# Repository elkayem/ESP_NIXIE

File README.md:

# ESP_NIXIE

Building a Nixie Clock is a time honored tradition among makers, and this is yet another DIY Nixie Clock project.  This one is unique in a few respects: 1) it uses an ESP8266 development board as the microcontroller, allowing it to automatically sync its time to NIST over WiFi, and 2) it features a 3D printed frame and hand-solderable PCB. 

These electronics have also been incorporated into a ceramic case by the talented artist [Jackson Fyfe](https://www.jacksonfyfeceramics.com/).  The case you see pictured above is one he created for me.  Head over to his website to see a number of his other stunning Nixie case designs, which he is selling as a limited release.

This repository contains the code, and schematics for driving a Nixie tube clock with a NodeMCU 1.0 ESP8266 development board.  STL files are also provided for a 3D printed case.  Two variants of the PCB and 3D printed cases are available, a PCB and case without a colon separator circuit, and a PCB and case with a colon separator circuit.  The code is the same, with a single #define statement that can be commented to compile the option without the separator circuit.   

When the clock is turned on for the first time, it will create a WiFi access point at ESPNIXIE that can be connected to using a computer or smartphone.  The user can use this access point to specify the WiFi network SSID and password.  This information is stored in EEPROM, so will not be needed the next time the clock is turned on.  It uses the Arduino [Wifi Manager](https://github.com/tzapu/WiFiManager) to create the access point.  

This clock includes a menu-driven OLED screen and rotary encoder, with menu options described below.  All settings are stored in EEPROM so they can be used after a power cycle.
* *Set UTC Offset.*  The user's local time zone is selected by adjusting the time offset from UTC time.
* *Auto DST.* This option enables/disables automatic daylight savings time.  The code includes rules for US Daylight Savings Time (second Sunday in March at 2am to first Sunday in November at 2am).  The code can easily be modified for rules in other countries.
* *12/24 Hours.* This option selects between 12 and 24 hour time formats.
* *Blink Colon.* This option is available if using a colon separator.  If enabled, it will blink the colon once per second, otherwise it will keep the colon on steady.  This option is not available if #define CLOCK_COLON is commented in the code.  
* *Protect Cathode.* Nixie tubes are susceptible to cathode poisoning when material from an active cathode sputters on the inactive cathodes.  This process can be reversed by occasionally cycling through all numbers for short durations.  When enabled, this feature will cycle through all the numbers at a 10 Hz rate for 5 seconds.  Besides protecting the cathodes, it also looks cool.  Time intervals ranging from 15 minutes to two hours can be selected.
* *Auto Shutoff.* When enabled, this feature will automatically turn off the tubes between designated hours (e.g., during the night), helping to preserve Nixie tube life.  The off and on times are selectable through a submenu.
* *Screensaver.* When enabled, a screensaver will activate on the OLED if the menu has been inactive for more than 60 seconds.  OLEDs are subject to screen burn-in, and this will help alleviate that issue.  Two screensaver options are available.  The first displays a scrolling image, and the second simply turns the OLED display off.
* *Show Zero.* This option allows the user to select whether the left most Nixie tube (tens place for the hour) should be turned off when it is zero, or whether zero should be shown.  
* *Reset Wifi.*  Selecting this will cause the ESP8266 to forget the current WiFi network.  The clock will reboot and set up a new WiFi access point at ESPNIXIE.   

In addition to these settings, holding the rotary encoder button down for more than three seconds will manually toggle the Nixie tubes on and off.  If the Auto Shutoff feature is enabled, the Nixies will stay on or off as selected until the next Auto Shutoff transition occurs, after which the Nixie tubes will turn on and off according to the Auto Shutoff schedule.

**Please PM me if you would like a set of printed circuit boards.** I have enough extras to make a few more ESP Nixie clocks.  

## Parts
* NodeMCU V1.0 (Amica board).  Clone boards often are unofficially labeled as V2
* 4 IN-14 Nixie Tubes
* 1 0.96" I2C 128x64 OLED display
* 1 Rotary Encoder
* 1 12VDC 1A Wall Adapter Power Supply
* 1 NCH6100HV High Voltage DC Power Supply (or equivalent)
* 1 Nixie Board PCB (options with or without colon separator circuit).  I've included the Eagle schematic, board layout, and gerber files in this repository for both options.  
* 2 15-pin female headers
* Lots of male breakaway headers (I haven't counted, buy a pack)
* 6 16-pin DIP IC Sockets
* 4 Nixie Tube PCBs.  Files included in this repository.  This can also easily be created using a strip board.
* 2 74HC595N shift registers
* 4 74141N BCD to Decimal Decoders (or K155ID1 Russian equivalents)
* 1 L7805 5V regulator (an additional heat sink is recommended)
* 1 0.33 uF capacitor
* 1 0.1 uF capacitor
* 1 3 Pin 5.08mm Pitch PCB Mount Screw Terminal  
* 1 2 Pin 5.08mm Pitch PCB Mount Screw Terminal 
* 4 15K Ohm resistors
* 1 20K Ohm resistor (used to illuminate decimal point if not using colon separator circuit.  However, I no longer recommend using this resistor for ascetic reasons.)
* Various M2 and M3 bolts
* 8 female-female short jumper cables.
* 1 MPSA42 Transistor (if using colon separator PCB)
* 2 200K Ohm resistors (if using colon separator circuit)
* 1 33K Ohm resistor (if using colon separator circuit)
* 1 IN-3 tube or 2 NE-2H tubes (if using colon separator circuit)

## Instructions
Most of these parts can be found on eBay or your favorite online Chinese retailer.  Although no longer manufactured, nixie tubes are still readily available, with the IN-14 selling for about $5-$10 per tube.  I recommend the NCH6100HV power supply, though there are many others out there capable of driving Nixie tubes.  The output voltage should be set to 170 V, which can be adjusted using an onboard potentiometer.  If selecting a different power supply, make sure it is capable of delivering at least 15 mA of continuous current at 170 V.

The Nixie Board PCB and tube PCBs must be manufactured by a PCB supplier.  The least expensive way to do this is to upload the gerber files (included as a .zip file) to one of several Chinese manufacturers such as JLCPCB, SchenZhen2U, or Seeed Studio.  pcbshopper.com allows a comparison between vendors.  Typical prices are $1-$3/board, with a minimum of 5 boards.  Recommended default settings are Layers: 2; PCB Thickness: 1.6mm; Surface Finish: HASL; Copper Weight: 1.  The main board is 100 x 80 mm, and the smaller tube boards are 20.7mm x 28.3mm.  

Solder headers, IC sockets, terminal blocks, resistors, voltage regulator, and capacitors to the board.  The 0.33 uF capacitor goes closest to the 2-pin terminal block.  The 20K Ohm resistor is marked as optional.  This will illuminate the decimal point between the hours and minutes.  Personally, I think it looks better without it and I did not use it, but it is there if others wish to use it.  Mount ICs, and NodeMCU to the headers and sockets.  

### Board Modifications
A few recommended modifications to the board are listed below. These changes will be incorporated into a future release of the board design. See figure below for suggested modifications to back of board.

**Button Pullup Resistor.** The encoder button is attached to pin D0 (GPIO16). This button requires a 10K pullup resistor to keep D0 high when the button is not depressed.  Unfortunately, the ESP-12E module on the NodeMCU board does not have a pullup resistor on this pin. It does have an LED which can sometimes function as a pullup resistor, so it is possible that your NodeMCU board will work just fine without this modification. NodeMCU boards with a blue LED on pin D0 require the additional 10K pullup resistor, while boards with a red LED can often function without one. See above figure for suggested configuration, with the non-grounded side of the button pin connected to 3.3V via a 10K resistor. The resistor can be soldered to the back of the board.

**Power Supply Shutdown Pin (Optional).** The auto shutoff feature will turn off the Nixie tubes at night to preserve Nixie tube life. This is primarily done by controlling the 74141N transistors. This still leaves the Nixie anodes connected to the 170V power supply, which can show a slight orange glow on the tubes visible in the dark. If using the NCH6100HV power supply, the 170V output can be completely turned off using the SHDN pin on the power supply, thereby completely eliminating the orange glow. To take advantage of this feature, solder a wire on the back side of the ESP_NIXIE board to the D3 pin, and connect the other end of the wire to the SHDN pin on the NCH6100HV. See purple wire on the above photo for pin location on the board. 

### Final Assembly
3D print the parts.  The top cover is printed on its side, and will need supports to prevent the tube holes from sagging.  Four tube sockets are required.  

Mount Nixie tubes through 3D printed tube sockets, and then through the tube PCBs.  Be careful to make sure the anode wire (the rear wire on the tube with an arrow pointing to it) goes through the PCB hole that connects to the center pin of the 7-pin header.  I should have marked it on the PCB.  Also, the side of the PCB with the traces is the top side.  It will not plug into the board if the tube is soldered to the wrong side.  

Mount the board to the 3D printed base with M3 bolts, and the OLED and HV power supply with M2 bolts.  Mount the rotary encoder to the back of the case.  Wire the 2-pin terminal block to the 12V wall power supply, and the 3-pin terminal block to the HV power supply using loose wire.  The GND can go to either side of the HV power supply, but make sure the terminal labeled 12V goes to Vin, and terminal labeled 170V goes to HV.  Connect the OLED to the four OLED pins on the board using jumper cables.  The rotary encoder should have three pins on one side and two on the other.  Connect the three pins to the 3 ENC headers on the board, and the two pins to the 2 BTN pins on the board.  If the jumper cables on the encoder are loose, you may wish to solder them on directly.  I did.

Flash software to ESP8266 using a micro-USB cable.  This can be done one of two ways: a) Use the compiled .bin files included in the repository, or b) compile and flash the firmware using the Arduino IDE.  For upload, I recommend using esptool at https://github.com/espressif/esptool to flash the esp8266.  After installing esptool (`pip install esptool`, or `python -m pip install esptool`), the following line is used to flash the ESP8266:

`esptool.py --port COM6 write_flash 0x0000 ESP_NIXIE_with_colon_separator.bin`
  
where COM6 should be replaced by whatever com port your device is plugged into. (In Windows, this is discoverable using the Device Monitor.) **Important:** I recommend unplugging the NodeMCU from the ESP_NIXIE board before flashing. This is because the encoder pins are attached to the Serial TX and RX pins, and can interfere with communication during upload.

Glue the case side panels to the top cover.  I use plastic epoxy.  Close the case and attach on the side corners using (optional) 1/2" #4 or #6 sheet metal screws.

When first powering the ESP Nixie clock, it will create a wireless access point called ESPCLOCK with default password: PASSWORD.  Connect to the wireless access point with a computer, and open 192.168.4.1 in a web browser if the configuration page does not automatically open.  This configuration page can be used to set your clock to connect to your home WiFi network.  

## Special Instructions for Compiling and Flashing Firmware Using Arduino IDE
There are a few configurable options in the code which may require recompiling. 

The default access point network name and password are hardcoded in lines, which may be changed as desired:

```
#define AP_NAME "ESPCLOCK"
#define AP_PASSWORD "PASSWORD"
```  

To compile the code without the colon separator PCB, comment out the following line.  This removes the option to enable/disable the circuit from blinking in the menu.

`#define CLOCK_COLON \\ Comment out if not using colon separator PCB`

Also note that if you do not see any text at all on the screen, I2C address of the OLED screen may be incorrect.  The code uses 0x3C, which is fairly common.  The I2C_Scanner can determine if your screen has a different address.  The address in the code can be modified and recompiled as necessary.

The steps to recompile and flash the firmware through the Arduino IDE are listed below.
1. Configure Arduino IDE
   1. Install Arduino IDE 1.8.10 (or later) from arduino.cc
   2. Open File>Preferences, and enter the following URL into "Additional Board Manager URLs": http://arduino.esp8266.com/stable/package_esp8266com_index.json
   3. Open Tools>Board>Board Manager and install the esp8266 boards.  ***Important Step:*** Use the "Select Version" pull down menu to select version **2.5.2**. At the present date (1/1/2020), the latest version (2.6.3) is not reliable with this code and electronics. If you are experiencing issues with the clock failing to reconnect to your wifi network after a power cycle, you may have missed this step and need to revert to 2.5.2.
   4. In the Tools menu, configure Board: NodeMCU 1.0 (ESP-12E Module), CPU Frequency: 80 MHz, Upload Speed: 115200.
2. Install the following libraries.  I have indicated which versions I am currently using (as of 1/1/2020), though in most cases later versions should work: NTPClient (3.2.0), WiFi (1.2.7), WiFiManager (0.15.0-beta), Time (1.6.0), Timezone (1.2.3), Adafruit_GFX (1.7.2), Adafruit_SSD1306 (2.0.3), and Switch (1.2.1).  All of these libraries are added through the Library Manager (Sketch > Include Library > Manage Libraries).   
3. Connect the NodeMCU board to your computer using a micro USB cable, and set Tools>Port to the new port that appears.  Your computer should automatically install the driver, but if it does not, you may need to manually download and install the CP2102 driver from http://www.silabs.com/products/mcu/pages/usbtouartbridgevcpdrivers.aspx.  **Suggestion:** I recommend unplugging the NodeMCU from the ESP_NIXIE board before flashing. This is because the encoder pins are attached to the Serial TX and RX pins, and can interfere with communication during upload. Note these pins should be open if the rotary encoder is in a detent position, so you may still be able to get away with flashing the NodeMCU while it is still attached to the ESP_NIXIE board. Be sure to unplug it from the wall first, though!
4. Press the Upload button to compile the sketch and upload to the NodeMCU.  The most common reason for failing to compile are an selecting the wrong board or not installing all the required libraries.

Hope you find this useful, and please do send me a picture if you make one of these!

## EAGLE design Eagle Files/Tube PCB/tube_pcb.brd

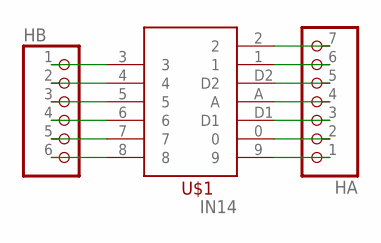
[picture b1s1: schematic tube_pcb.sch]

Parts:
HA: PINHD-1X7; 1X07
HB: PINHD-1X6; 1X06
U$1: IN14

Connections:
0: HA.2, U$1.0
1: HA.6, U$1.1
2: HA.7, U$1.2
3: HB.1, U$1.3
4: HB.2, U$1.4
5: HB.3, U$1.5
6: HB.4, U$1.6
7: HB.5, U$1.7
8: HB.6, U$1.8
9: HA.1, U$1.9
A: HA.4, U$1.A
D1: HA.3, U$1.D1
D2: HA.5, U$1.D2

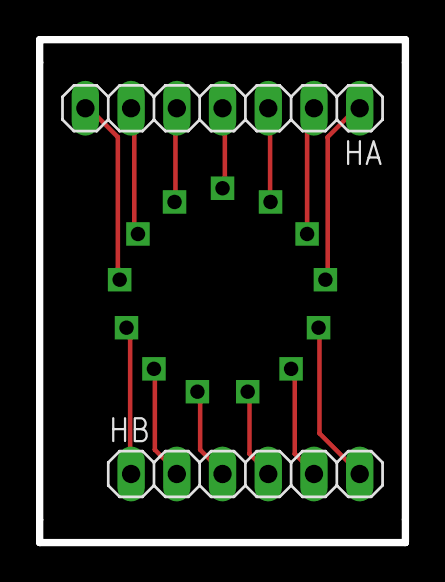
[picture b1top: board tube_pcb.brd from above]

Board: 2 copper layers, 20.3 x 27.9 mm, 3 parts (0 on the bottom side), 13 nets.

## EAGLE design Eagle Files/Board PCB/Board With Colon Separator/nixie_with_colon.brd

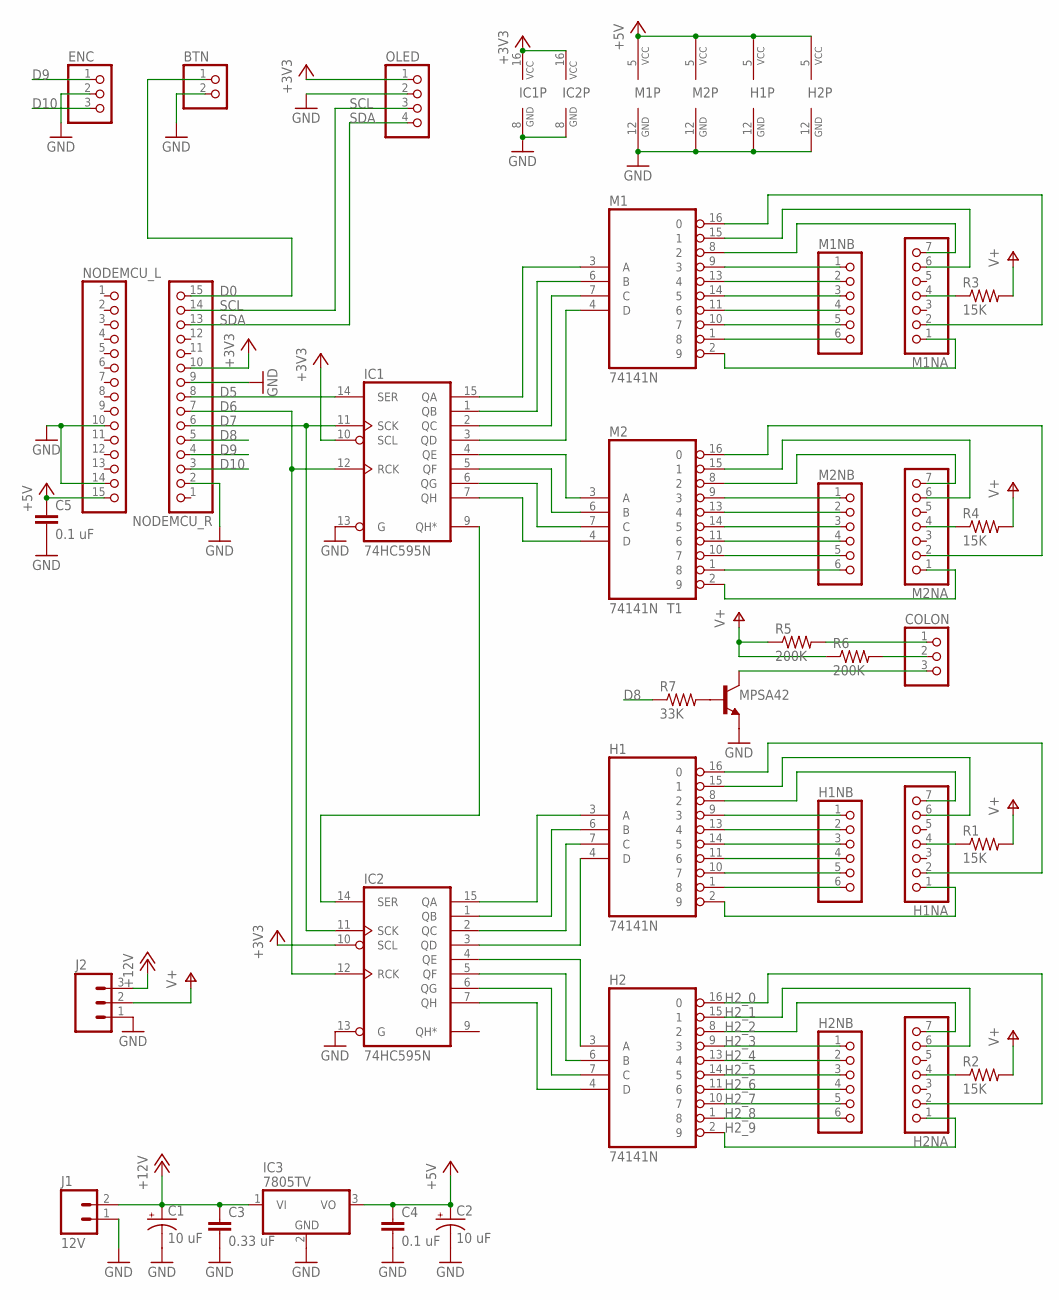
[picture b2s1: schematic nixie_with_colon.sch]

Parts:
BTN: PINHD-1X2; 1X02
C1, C2: 10 uF; E2,5-6
C3: 0.33 uF; C050-025X075
C4, C5: 0.1 uF; C050-025X075
COLON: PINHD-1X3; 1X03
ENC: PINHD-1X3; 1X03
H1, H2: 74141N; DIL16
H1NA, H2NA: PINHD-1X7; 1X07
H1NB, H2NB: PINHD-1X6; 1X06
IC1, IC2: 74HC595N; DIL16
IC3: 7805TV; TO220V
J1: 12V; SCREWTERMINAL-5MM-2
J2: M03-SCREW-5MM; SCREWTERMINAL-5MM-3
M1, M2: 74141N; DIL16
M1NA, M2NA: PINHD-1X7; 1X07
M1NB, M2NB: PINHD-1X6; 1X06
NODEMCU_L: PINHD-1X15; 1X15
NODEMCU_R: PINHD-1X15; 1X15
OLED: PINHD-1X4; 1X04
R1, R2, R3, R4: 15K; 0207/10
R5, R6: 200K; 0207/10
R7: 33K; 0207/10
T1: MPSA42; TO92-EBC

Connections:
+3V3: IC1.10 (SCL), IC1.16 (VCC), IC2.10 (SCL), IC2.16 (VCC), NODEMCU_R.10, OLED.1
+5V: C2.+, C4.1, C5.1, H1.5 (VCC), H2.5 (VCC), IC3.3 (VO), M1.5 (VCC), M2.5 (VCC), NODEMCU_L.15
+12V: C1.+, C3.1, IC3.1 (VI), J1.2, J2.3
D0: BTN.1, NODEMCU_R.15
D5: IC1.14 (SER), NODEMCU_R.8
D6: IC1.12 (RCK), IC2.12 (RCK), NODEMCU_R.7
D7: IC1.11 (SCK), IC2.11 (SCK), NODEMCU_R.6
D8: NODEMCU_R.5, R7.1
D9: ENC.1, NODEMCU_R.4
D10: ENC.3, NODEMCU_R.3
GND: BTN.2, C1.-, C2.-, C3.2, C4.2, C5.2, ENC.2, H1.12 (GND), H2.12 (GND), IC1.8 (GND), IC1.13 (G), IC2.8 (GND), IC2.13 (G), IC3.2 (GND), J1.1, J2.1, M1.12 (GND), M2.12 (GND), NODEMCU_L.10, NODEMCU_L.14, NODEMCU_R.2, NODEMCU_R.9, OLED.2, T1.E
H2_0: H2.16 (0), H2NA.2
H2_1: H2.15 (1), H2NA.6
H2_2: H2.8 (2), H2NA.7
H2_3: H2.9 (3), H2NB.1
H2_4: H2.13 (4), H2NB.2
H2_5: H2.14 (5), H2NB.3
H2_6: H2.11 (6), H2NB.4
H2_7: H2.10 (7), H2NB.5
H2_8: H2.1 (8), H2NB.6
H2_9: H2.2 (9), H2NA.1
unnamed: H1.16 (0), H1NA.2
unnamed: H1.2 (9), H1NA.1
unnamed: H1.9 (3), H1NB.1
unnamed: H1.13 (4), H1NB.2
unnamed: H1.14 (5), H1NB.3
unnamed: H1.11 (6), H1NB.4
unnamed: H1.10 (7), H1NB.5
unnamed: H1.1 (8), H1NB.6
unnamed: H1.8 (2), H1NA.7
unnamed: H1.15 (1), H1NA.6
unnamed: H1NA.4, R1.1
unnamed: COLON.2, R6.2
unnamed: COLON.1, R5.2
unnamed: COLON.3, T1.C
unnamed: R7.2, T1.B
unnamed: H2NA.4, R2.1
unnamed: M1.16 (0), M1NA.2
unnamed: M1.9 (3), M1NB.1
unnamed: M1.13 (4), M1NB.2
unnamed: M1.14 (5), M1NB.3
unnamed: M1.11 (6), M1NB.4
unnamed: M1.10 (7), M1NB.5
unnamed: M1.1 (8), M1NB.6
unnamed: M1.2 (9), M1NA.1
unnamed: M1.8 (2), M1NA.7
unnamed: M1.15 (1), M1NA.6
unnamed: M1NA.4, R3.1
unnamed: M2.16 (0), M2NA.2
unnamed: M2.9 (3), M2NB.1
unnamed: M2.13 (4), M2NB.2
unnamed: M2.14 (5), M2NB.3
unnamed: M2.11 (6), M2NB.4
unnamed: M2.10 (7), M2NB.5
unnamed: M2.1 (8), M2NB.6
unnamed: M2.2 (9), M2NA.1
unnamed: M2.8 (2), M2NA.7
unnamed: M2.15 (1), M2NA.6
unnamed: M2NA.4, R4.1
unnamed: IC1.15 (QA), M1.3 (A)
unnamed: IC1.1 (QB), M1.6 (B)
unnamed: IC1.2 (QC), M1.7 (C)
unnamed: IC1.3 (QD), M1.4 (D)
unnamed: IC1.4 (QE), M2.3 (A)
unnamed: IC1.5 (QF), M2.6 (B)
unnamed: IC1.6 (QG), M2.7 (C)
unnamed: IC1.7 (QH), M2.4 (D)
unnamed: H1.3 (A), IC2.15 (QA)
unnamed: H1.6 (B), IC2.1 (QB)
unnamed: H1.7 (C), IC2.2 (QC)
unnamed: H1.4 (D), IC2.3 (QD)
unnamed: H2.3 (A), IC2.4 (QE)
unnamed: H2.6 (B), IC2.5 (QF)
unnamed: H2.7 (C), IC2.6 (QG)
unnamed: H2.4 (D), IC2.7 (QH)
unnamed: IC1.9 (QH*), IC2.14 (SER)
SCL: NODEMCU_R.14, OLED.3
SDA: NODEMCU_R.13, OLED.4
V+: J2.2, R1.2, R2.2, R3.2, R4.2, R5.1, R6.1

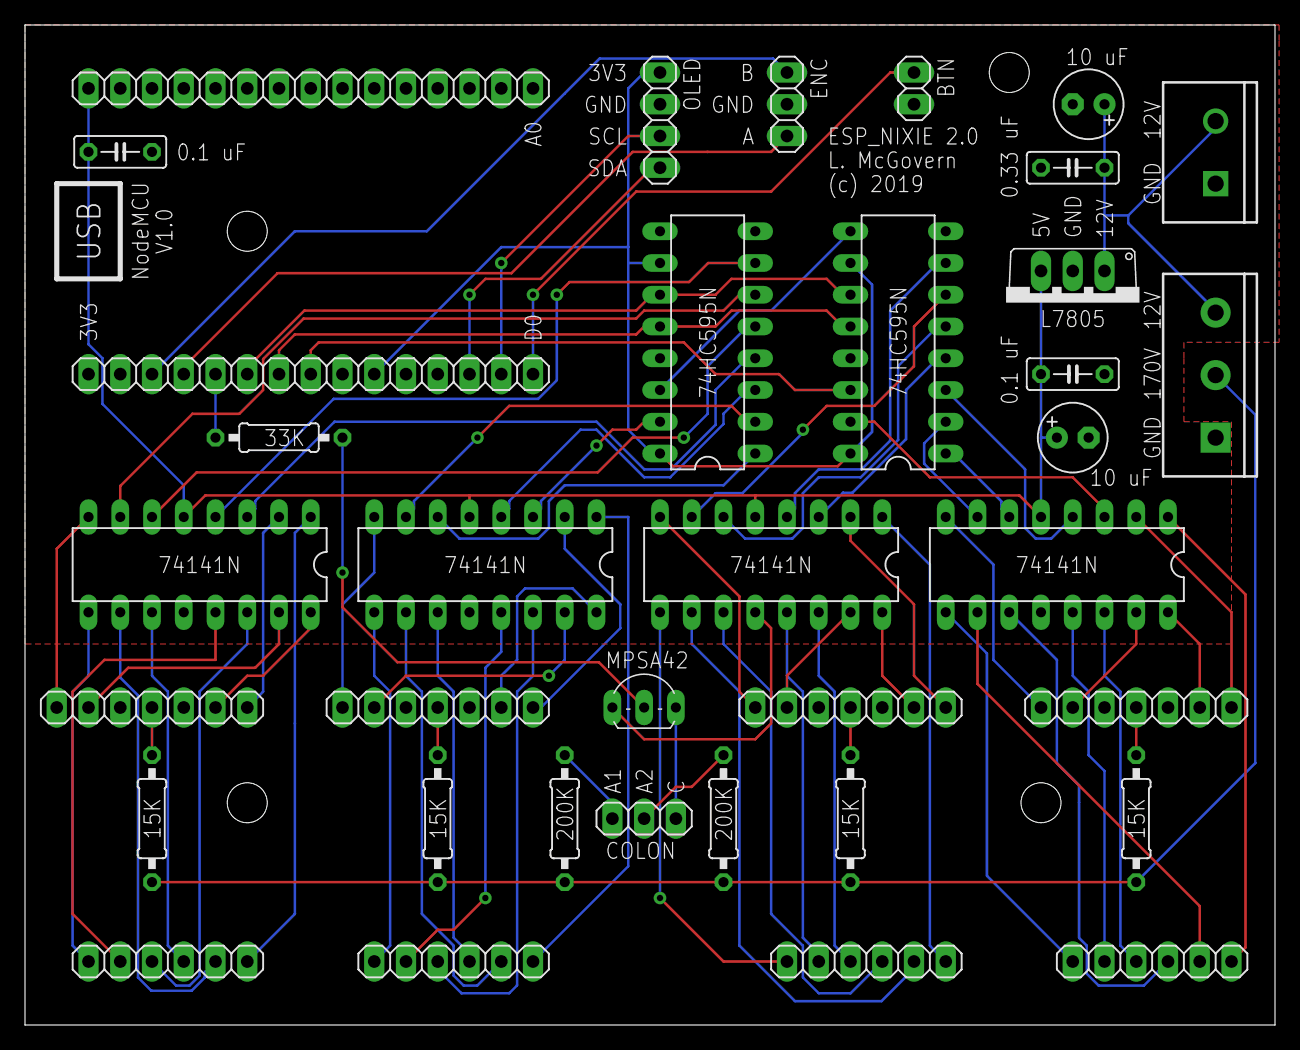
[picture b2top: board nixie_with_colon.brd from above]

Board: 2 copper layers, 100.0 x 80.0 mm, 36 parts (0 on the bottom side), 79 nets.

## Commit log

2016-12-02 Check in source code and related files.
2016-12-02 Make Switch an Arduino library and remove from repository
2016-12-03 update photos
2016-12-03 correct readme
2016-12-03 correcting readme file
2016-12-03 update images
2017-10-11 Add compiled binary.
2018-06-02 Added new features: 1) cathode protection pattern, 2) 12/24 hour option, 3) Automatically turn off display during settable hours to save nixie life, 4) Option to show or not show zero in 10's place o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
2018-06-02 Minor update to settings menu
2018-06-03 Updated cathode protection logic. Added schematic and board pdfs.
2018-06-03 Update cathode protection logic
2018-06-04 Fix bug when changing UTC and DST settings
2018-06-06 Implemented manual Nixie on/off feature.
2018-06-08 Update auto shutoff code
2018-06-09 Fixed WiFi reset issue
2019-01-05 Added code to blink optional colon circuit
2019-01-05 Colon separator updates
2019-01-13 Add colon separator PCB and case
2019-01-20 Add new images
2019-02-02 Added OLED screensaver option
2019-02-03 screensaver updates
2019-02-17 New images
2019-02-17 update image
2019-12-24 Added NCH6100HV SHDN pin support.
2019-12-29 Pull-up resistor update
2020-01-01 Revert to ESP8266 core 2.5.2, add new photos

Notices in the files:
Eagle Files/Board PCB/Board With Colon Separator/nixie_with_colon.brd:
(c) 2019
parts and their libraries:
SparkFun-Connectors: Licensing: Creative Commons ShareAlike 4.0 International - https://creativecommons.org/licenses/by-sa/4.0
